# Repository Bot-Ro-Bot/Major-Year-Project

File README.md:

## A Major Project On "[Human-Computer Interaction using Neuromuscular Signals](http://conference.ioe.edu.np/publications/ioegc12/IOEGC-12-082-12118.pdf)"

### ABSTRACT
Subvocal speech or internal articulation is a form of non-voiced speech that is voluntarily
spoken. It is generated alongside the micromovement of the articulatory muscles, imperceptible to others. However, the faint sEMG (surface Electromyography) signals
can still be detected and analyzed to predict the internally articulated speech. This
research project attempts to study this very phenomenon and its possible use case in
human-computer interaction. By extracting sEMG signals from several of these
articulators and processing the extracted signals, prominent features of a particular
utterance can be isolated. They can be used to train a machine-learning model. After training
the model on several such utterances, accurate predictions of the utterances can be made
which can be further utilized to perform a predefined action on a remote computer. This
research also explores improving traditional speech recognition models by possible
augmentation of both approaches.

### Team Members: 
#### Rabin Nepal https://github.com/Bot-Ro-Bot
#### Rhimesh Lwagun https://github.com/riderman10000
#### Sanjay Rijal https://github.com/zovelsanj
#### Upendra Subedi https://github.com/upendrasubedi

The full version of the thesis is also publicly available at [ResearchGate](https://www.researchgate.net/publication/380073456_A_Major_Project_Report_On_Human-Computer_Interaction_Using_Neuromuscular_Signals).
### Citation
```
@InProceedings{IOEGC-12-082-12118,
    author       = {Rhimesh Lwagun and  Sanjay Rijal and  Rabin Nepal and  Upendra Subedi and  Dinesh Baniya Kshatri},
    title        = {{Silent Speech Recognition in Nepali}},
    pages        = {628 -- 635},
    booktitle    = {Proceedings of 12th IOE Graduate Conference},
    year         = {2022},
    volume       = {12},
    month        = {October},
    organization = {Institute of Engineering, Tribhuvan University, Nepal}
}
```

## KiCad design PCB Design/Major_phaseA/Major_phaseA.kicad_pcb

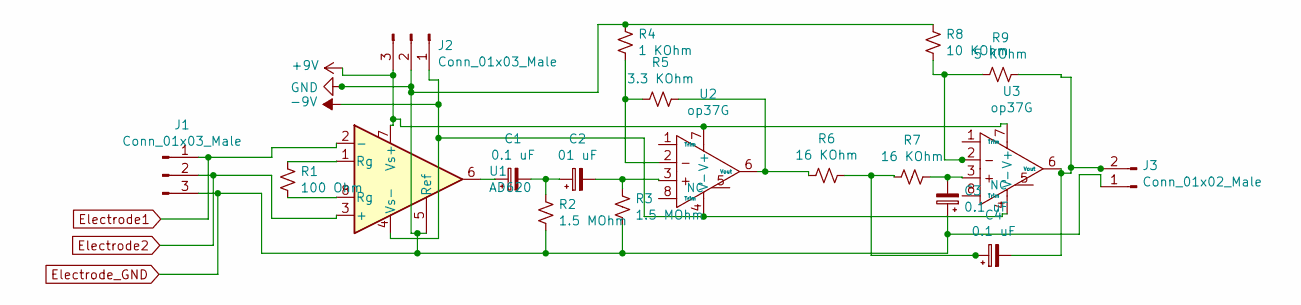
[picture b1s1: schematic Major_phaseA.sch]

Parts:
C1, C3, C4: 0.1 uF; CP_Radial_D6.3mm_P2.50mm
C2: 01 uF; CP_Radial_D6.3mm_P2.50mm
J1, J2: Conn_01x03_Male; PinHeader_1x03_P2.54mm_Vertical
J3: Conn_01x02_Male; PinHeader_1x02_P2.54mm_Vertical
R1: 100 Ohm; R_Axial_DIN0207_L6.3mm_D2.5mm_P7.62mm_Horizontal
R2, R3: 1.5 MOhm; R_Axial_DIN0411_L9.9mm_D3.6mm_P12.70mm_Horizontal
R4: 1 KOhm; R_Axial_DIN0207_L6.3mm_D2.5mm_P7.62mm_Horizontal
R5: 3.3 KOhm; R_Axial_DIN0207_L6.3mm_D2.5mm_P7.62mm_Horizontal
R6, R7: 16 KOhm; R_Axial_DIN0207_L6.3mm_D2.5mm_P7.62mm_Horizontal
R8: 10 KOhm; R_Axial_DIN0207_L6.3mm_D2.5mm_P7.62mm_Horizontal
R9: 5 KOhm; R_Axial_DIN0207_L6.3mm_D2.5mm_P7.62mm_Horizontal
U1: AD620; DIP-8_W7.62mm
U2, U3: op37G; DIP-8_W7.62mm

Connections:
+9V: J2.3, U1.7 (Vs+), U2.7 (V+), U3.7 (V+)
-9V: J2.1, U1.4 (Vs-), U2.4 (V-), U3.4 (V-)
Electrode1: J1.1, U1.2 (-)
Electrode2: J1.2, U1.3 (+)
Electrode_GND: C3.1, J1.3, J2.2, J3.1, R2.2, R3.2, R4.1, R8.1, U1.5 (Ref)
unnamed: C1.1, U1.6
unnamed: C1.2, C2.1, R2.1
unnamed: C2.2, R3.1, U2.3
unnamed: C3.2, R7.1, U3.3
unnamed: C4.1, R6.1, R7.2
unnamed: C4.2, J3.2, R9.1, U3.6 (Vout)
unnamed: R1.1, U1.1 (Rg)
unnamed: R1.2, U1.8 (Rg)
unnamed: R4.2, R5.2, U2.2
unnamed: R5.1, R6.2, U2.6 (Vout)
unnamed: R8.2, R9.2, U3.2

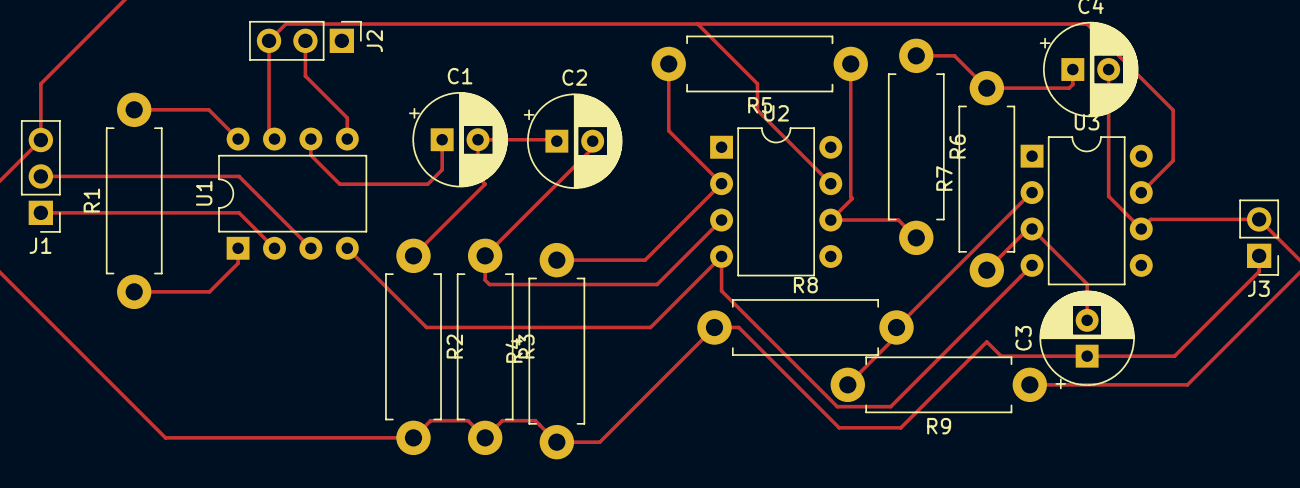
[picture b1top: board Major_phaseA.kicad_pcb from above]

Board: 2 copper layers, 19 parts (0 on the bottom side), 16 nets.

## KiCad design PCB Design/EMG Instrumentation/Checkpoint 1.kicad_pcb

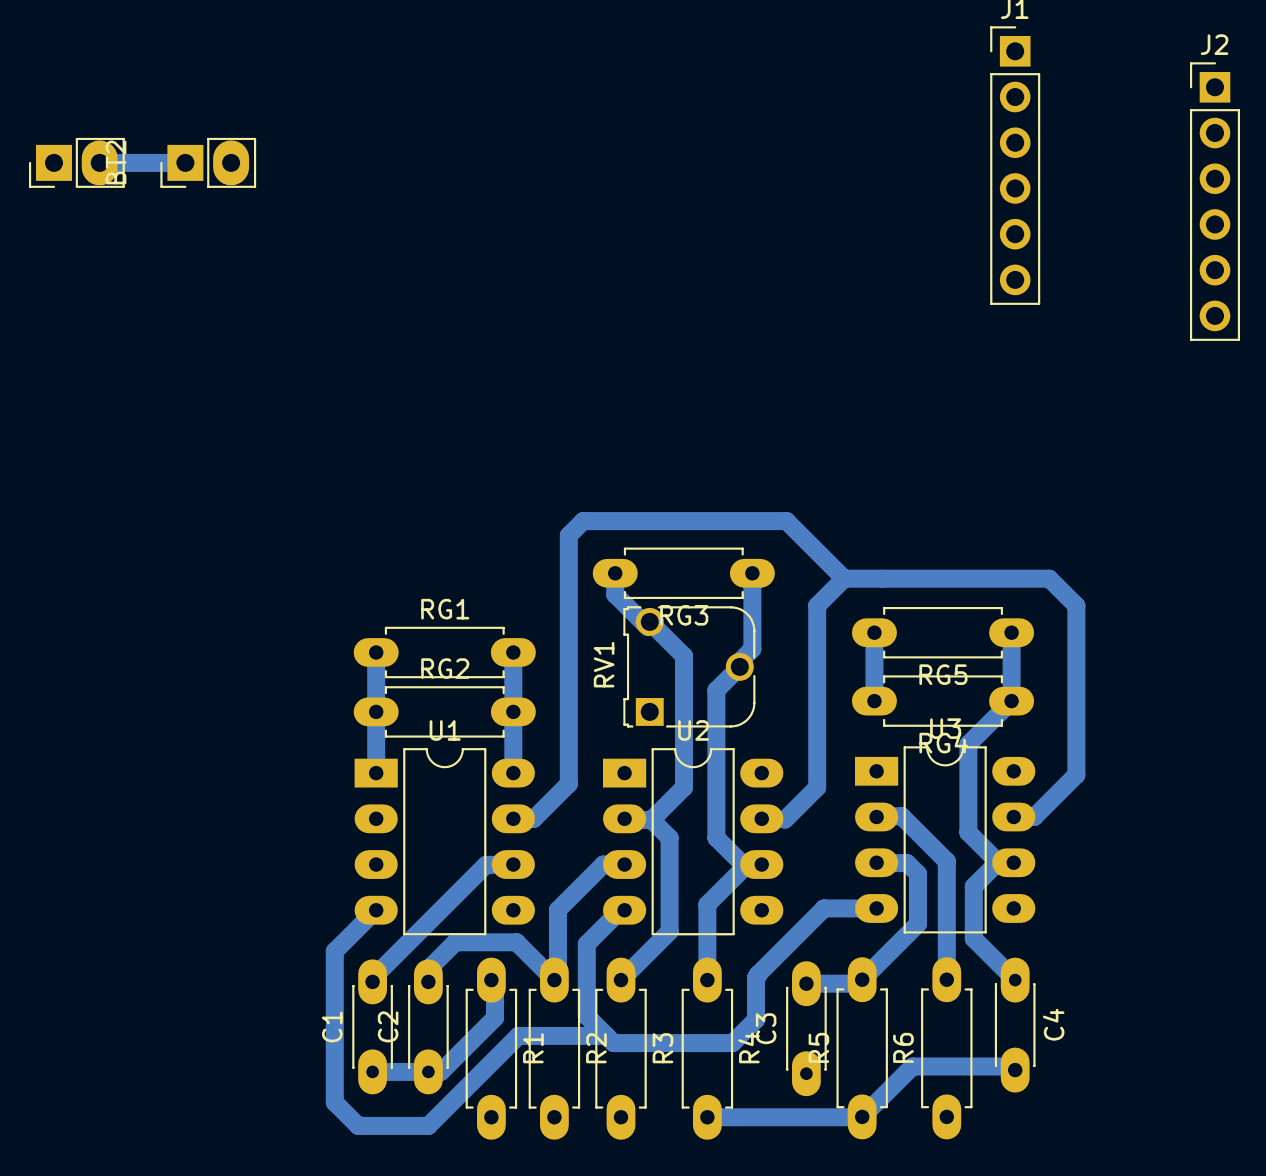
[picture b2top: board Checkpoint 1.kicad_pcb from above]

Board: 2 copper layers, 23 parts (0 on the bottom side), 15 nets.

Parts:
BT1, BT2: 9V; 9V_Battery_Connector
C1, C2, C3, C4: 0.1uF; Disc_Capacitor_Longpads
J1: Input Terminal; PinHeader_1x06_P2.54mm_Vertical
J2: Output Terminal; PinHeader_1x06_P2.54mm_Vertical
R1, R2: 1.5M; Axial_Resistor_Longpads
R3: 1K; Axial_Resistor_Longpads
R4, R5: 16K; Axial_Resistor_Longpads
R6: 10K; Axial_Resistor_Longpads
RG1, RG2: 100; Axial_Resistor_Longpads
RG3: 10K; Axial_Resistor_Longpads
RG4: 5K; Axial_Resistor_Longpads
RG5: 10k; Axial_Resistor_Longpads
RV1: 100k; Potentiometer_Runtron_RM-065_Vertical
U1: AD620; DIP-8_W7.62mm_LongPads
U2, U3: OP37G; DIP-8_W7.62mm_LongPads

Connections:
+9V: BT1.1, U1.7, U2.7, U3.7
-9V: BT2.2, U1.4, U2.4, U3.4
/Channel 1/Channel_6_OUT: C4.1, RG4.1, RG5.1, U3.6
/Channel 1/SIG_1: C1.2, U1.6
/Channel 1/SIG_2: C2.2, R2.1, U2.3
/Channel 1/SIG_3: R4.1, RG3.1, RV1.2, U2.6
BATT_GND: BT1.2, BT2.1, C3.1, J2.6, R1.2, R2.2, R3.2, R6.1, U1.5
unnamed: C1.1, C2.1, R1.1
unnamed: C3.2, R5.2, U3.3
unnamed: C4.2, R4.2, R5.1
unnamed: R3.1, RG3.2, RV1.3, U2.2
unnamed: R6.2, RG4.2, RG5.2, U3.2
unnamed: RG1.1, RG2.1, U1.1
unnamed: RG1.2, RG2.2, U1.8
REFERENCE: J1.6, U1.2

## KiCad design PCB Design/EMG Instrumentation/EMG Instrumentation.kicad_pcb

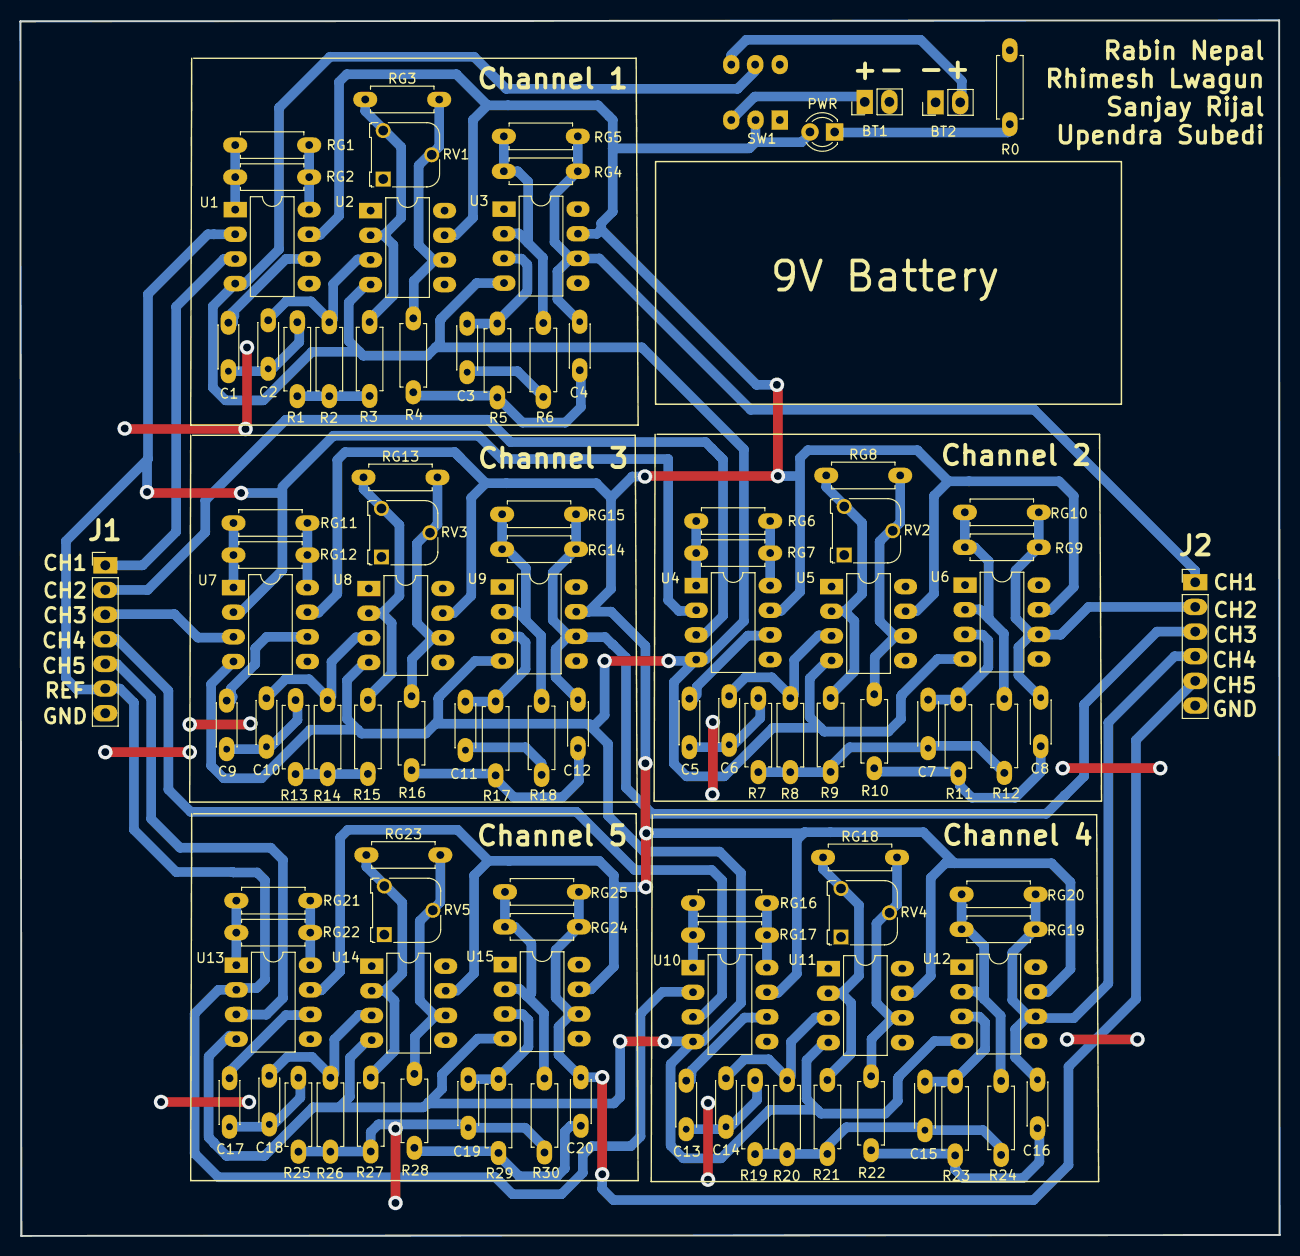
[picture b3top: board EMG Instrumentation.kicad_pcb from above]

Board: 2 copper layers, 129.8 x 125.2 mm, 102 parts (0 on the bottom side), 67 nets.

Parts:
BT1, BT2: 9V; 9V_Battery_Connector
C1, C2, C3, C4, C5, C6, C7, C8, C9, C10, C11, C12, C13, C14, C15, C16, C17, C18, C19, C20: 0.1uF; Disc_Capacitor_Longpads
J1: Input Terminal; PinHeader_1x07_P2.54mm_Vertical
J2: Output Terminal; PinHeader_1x06_P2.54mm_Vertical
PWR: Red; LED_D3.0mm
R0: 2.5K; Axial_Resistor_Longpads
R1, R2, R7, R8, R13, R14, R19, R20, R25, R26: 1.5M; Axial_Resistor_Longpads
R3, R9, R15, R21, R27: 1K; Axial_Resistor_Longpads
R4, R5, R10, R11, R16, R17, R22, R23, R28, R29: 16K; Axial_Resistor_Longpads
R6, R12, R18, R24, R30: 10K; Axial_Resistor_Longpads
RG1, RG2, RG6, RG7, RG11, RG12, RG16, RG17, RG21, RG22: 100; Axial_Resistor_Longpads
RG3, RG8, RG13, RG18, RG23: 10K; Axial_Resistor_Longpads
RG4, RG9, RG14, RG19, RG24: 5K; Axial_Resistor_Longpads
RG5, RG10, RG15, RG20, RG25: 10k; Axial_Resistor_Longpads
RV1, RV2, RV3, RV4, RV5: 100k; Trim_Potentiometer
SW1: Switch; Microswitch
U1, U4, U7, U10, U13: AD620; DIP-8_W7.62mm_LongPads
U2, U3, U5, U6, U8, U9, U11, U12, U14, U15: OP37G; DIP-8_W7.62mm_LongPads

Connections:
+9V: PWR.2, SW1.2, U1.7, U2.7, U3.7, U4.7, U5.7, U6.7, U7.7, U8.7, U9.7, U10.7, U11.7, U12.7, U13.7, U14.7, U15.7
-9V: SW1.5, U1.4, U2.4, U3.4, U4.4, U5.4, U6.4, U7.4, U8.4, U9.4, U10.4, U11.4, U12.4, U13.4, U14.4, U15.4
/Channel 1/SIG_1: C1.2, U1.6
/Channel 1/SIG_2: C2.2, R2.1, U2.3
/Channel 1/SIG_3: R4.1, RG3.1, RV1.2, U2.6
/Channel 2/SIG_1: C5.2, U4.6
/Channel 2/SIG_2: C6.2, R8.1, U5.3
/Channel 2/SIG_3: R10.1, RG8.1, RV2.2, U5.6
/Channel 3/SIG_1: C9.2, U7.6
/Channel 3/SIG_2: C10.2, R14.1, U8.3
/Channel 3/SIG_3: R16.1, RG13.1, RV3.2, U8.6
/Channel 4/SIG_1: C13.2, U10.6
/Channel 4/SIG_2: C14.2, R20.1, U11.3
/Channel 4/SIG_3: R22.1, RG18.1, RV4.2, U11.6
/Channel 5/SIG_1: C17.2, U13.6
/Channel 5/SIG_2: C18.2, R26.1, U14.3
/Channel 5/SIG_3: R28.1, RG23.1, RV5.2, U14.6
BATT_GND: BT1.2, BT2.1, C3.1, C7.1, C11.1, C15.1, C19.1, J1.7, J2.6, R0.2, R1.2, R2.2, R3.2, R6.1, R7.2, R8.2, R9.2, R12.1, R13.2, R14.2, R15.2, R18.1, R19.2, R20.2, R21.2, R24.1, R25.2, R26.2, R27.2, R30.1, U1.5, U4.5, U7.5, U10.5, U13.5
Channel_1_IN: J1.1, U1.3
Channel_1_OUT: C4.1, J2.1, RG4.1, RG5.1, U3.6
Channel_2_IN: J1.2, U4.3
Channel_2_OUT: C8.1, J2.2, RG9.1, RG10.1, U6.6
Channel_3_IN: J1.3, U7.3
Channel_3_OUT: C12.1, J2.3, RG14.1, RG15.1, U9.6
Channel_4_IN: J1.4, U10.3
Channel_4_OUT: C16.1, J2.4, RG19.1, RG20.1, U12.6
Channel_5_IN: J1.5, U13.3
Channel_5_OUT: C20.1, J2.5, RG24.1, RG25.1, U15.6
unnamed: BT1.1, SW1.3
unnamed: BT2.2, SW1.6
unnamed: C1.1, C2.1, R1.1
unnamed: C3.2, R5.2, U3.3
unnamed: C4.2, R4.2, R5.1
unnamed: C5.1, C6.1, R7.1
unnamed: C7.2, R11.2, U6.3
unnamed: C8.2, R10.2, R11.1
unnamed: C9.1, C10.1, R13.1
unnamed: C11.2, R17.2, U9.3
unnamed: C12.2, R16.2, R17.1
unnamed: C13.1, C14.1, R19.1
unnamed: C15.2, R23.2, U12.3
unnamed: C16.2, R22.2, R23.1
unnamed: C17.1, C18.1, R25.1
unnamed: C19.2, R29.2, U15.3
unnamed: C20.2, R28.2, R29.1
unnamed: PWR.1, R0.1
unnamed: R3.1, RG3.2, RV1.3, U2.2
unnamed: R6.2, RG4.2, RG5.2, U3.2
unnamed: R9.1, RG8.2, RV2.3, U5.2
unnamed: R12.2, RG9.2, RG10.2, U6.2
unnamed: R15.1, RG13.2, RV3.3, U8.2
unnamed: R18.2, RG14.2, RG15.2, U9.2
unnamed: R21.1, RG18.2, RV4.3, U11.2
unnamed: R24.2, RG19.2, RG20.2, U12.2
unnamed: R27.1, RG23.2, RV5.3, U14.2
unnamed: R30.2, RG24.2, RG25.2, U15.2
unnamed: RG1.1, RG2.1, U1.1
unnamed: RG1.2, RG2.2, U1.8
unnamed: RG6.1, RG7.1, U4.1
unnamed: RG6.2, RG7.2, U4.8
unnamed: RG11.1, RG12.1, U7.1
unnamed: RG11.2, RG12.2, U7.8
unnamed: RG16.1, RG17.1, U10.1
unnamed: RG16.2, RG17.2, U10.8
unnamed: RG21.1, RG22.1, U13.1
unnamed: RG21.2, RG22.2, U13.8
REFERENCE: J1.6, U1.2, U4.2, U7.2, U10.2, U13.2

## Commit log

2020-04-18 import list update garne sabbai jana milera
2020-05-03 Updated some functions
2020-10-14 Updated abstract of the project
2020-10-14 Added github accounts for all member
2020-10-14 rearranged files
2020-10-14 Added report and slides
2020-12-11 adding dataset, also contains codes
2020-12-11 added dataset with parsing codes
2020-12-15 removed import list
2020-12-15 added files in references
2020-12-17 added rabin sir data
2020-12-22 SR US dataset
2020-12-23 deleted file hero
2020-12-23 added pcb files
2020-12-23 test
2020-12-23 updatin
2020-12-23 Fixed Empty List #2
2020-12-23 Fixed Issue Empty list #2
2020-12-24 dataset RN mouthed reply set as bak
2020-12-27 corrected spelling error of subtract
2020-12-30 added pickel implementaion
2020-12-30 repickle parser
2020-12-30 my commit
2020-12-31 dataset added
2021-02-03 added features
2021-02-12 remaining dataset
2021-02-12 bak a file
2021-02-12 CNN implemenation
2021-02-18 ricker and aftermain
2021-02-18 update from upstream
2021-02-18 hello
2021-02-18 Revert "hello"
    This reverts commit 7a3f83f05bbae9b5f2eb677ddcedde3159f4c30a.
2021-02-18 haha
2021-02-18 nothing changed just doing fun
2021-02-19 upstream updates
2021-02-19 terminal output
2021-02-20 mod. after_main
2021-02-23 added jupyter-notebook files
2021-02-23 added run all file
2021-02-23 change in emgprocessing
2021-02-24 run all changes
2021-02-27 maintain flow v1
2021-02-28 resolving some conflicts v1
2021-02-28 added saved models
2021-02-28 changes to aftermain.py
2021-02-28 test1
2021-03-01 small typo
2022-04-13 final docs
2022-04-13 references all
2023-05-05 added BibTex
2023-05-06 added references and BibTex (#18)
    * final docs
    * references all
    * added BibTex
2023-08-04 added link, fixed grammar
2024-04-25 Removed thesis with bookmark error in TOC
    - final black binding version thesis is at `Documentation/major_final_1614433681.pdf`
2024-05-18 added thesis link
